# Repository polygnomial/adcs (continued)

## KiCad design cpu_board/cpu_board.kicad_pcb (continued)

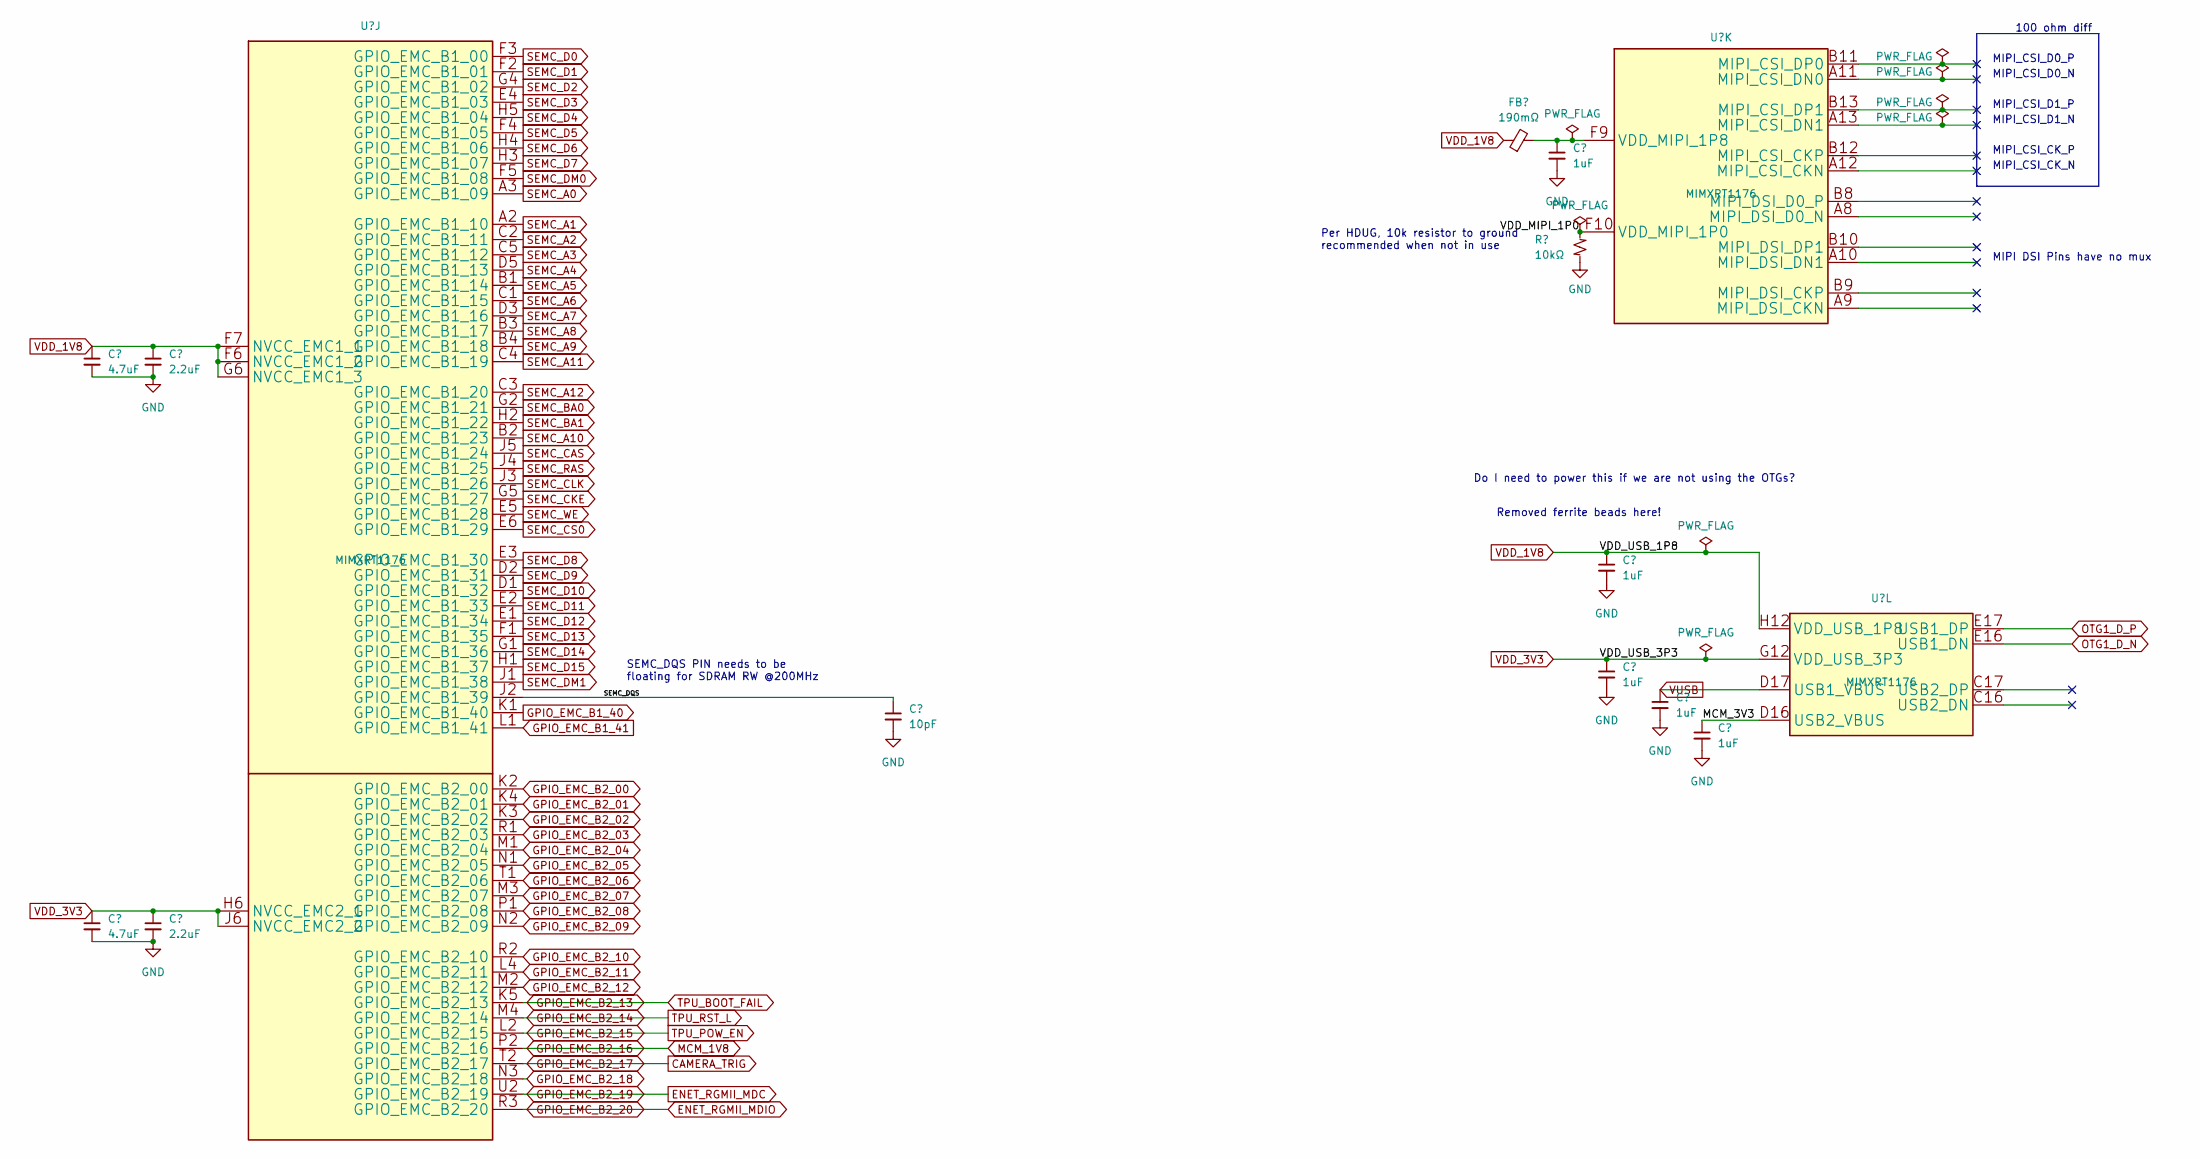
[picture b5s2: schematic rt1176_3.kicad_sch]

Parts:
C5: 10pF; Perfect_0201
C51, C52: 4.7uF; Perfect_0201
C53, C54: 2.2uF; Perfect_0201
C56, C58, C59, C61: 1uF; Perfect_0201
C60: 1uF; Perfect_0402
FB3: 190mΩ; Perfect_0402; JLCPCB P/N C85812
R10: 10kΩ; Perfect_0201
U2: MIMXRT1176; U_MIMXRT1176DVMAA_NXP; JLCPCB P/N C1020267

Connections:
/RT1176 #3/MCM_3V3: C61.1, U2.D16 (USB2_VBUS)
/RT1176 #3/SEMC_DQS: C5.1, U2.J2 (GPIO_EMC_B1_39)
CAMERA_TRIG: U2.T2 (GPIO_EMC_B2_17); also elsewhere on the board
ENET_RGMII_MDC: U2.U2 (GPIO_EMC_B2_19); also elsewhere on the board
ENET_RGMII_MDIO: U2.R3 (GPIO_EMC_B2_20); also elsewhere on the board
GPIO_EMC_B1_40: U2.K1 (GPIO_EMC_B1_40); also elsewhere on the board
GPIO_EMC_B1_41: U2.L1 (GPIO_EMC_B1_41); also elsewhere on the board
GPIO_EMC_B2_00: U2.K2 (GPIO_EMC_B2_00); also elsewhere on the board
GPIO_EMC_B2_01: U2.K4 (GPIO_EMC_B2_01); also elsewhere on the board
GPIO_EMC_B2_02: U2.K3 (GPIO_EMC_B2_02); also elsewhere on the board
GPIO_EMC_B2_03: U2.R1 (GPIO_EMC_B2_03); also elsewhere on the board
GPIO_EMC_B2_04: U2.M1 (GPIO_EMC_B2_04); also elsewhere on the board
GPIO_EMC_B2_05: U2.N1 (GPIO_EMC_B2_05); also elsewhere on the board
GPIO_EMC_B2_06: U2.T1 (GPIO_EMC_B2_06); also elsewhere on the board
GPIO_EMC_B2_07: U2.M3 (GPIO_EMC_B2_07); also elsewhere on the board
GPIO_EMC_B2_08: U2.P1 (GPIO_EMC_B2_08); also elsewhere on the board
GPIO_EMC_B2_09: U2.N2 (GPIO_EMC_B2_09); also elsewhere on the board
GPIO_EMC_B2_10: U2.R2 (GPIO_EMC_B2_10); also elsewhere on the board
GPIO_EMC_B2_11: U2.L4 (GPIO_EMC_B2_11); also elsewhere on the board
GPIO_EMC_B2_12: U2.M2 (GPIO_EMC_B2_12); also elsewhere on the board
GPIO_EMC_B2_13: U2.K5 (GPIO_EMC_B2_13); also elsewhere on the board
GPIO_EMC_B2_14: U2.M4 (GPIO_EMC_B2_14); also elsewhere on the board
GPIO_EMC_B2_15: U2.L2 (GPIO_EMC_B2_15); also elsewhere on the board
GPIO_EMC_B2_16: U2.P2 (GPIO_EMC_B2_16); also elsewhere on the board
GPIO_EMC_B2_18: U2.N3 (GPIO_EMC_B2_18); also elsewhere on the board
unnamed: C56.1, FB3.2, U2.F9 (VDD_MIPI_1P8)
OTG1_D_N: U2.E16 (USB1_DN); also elsewhere on the board
OTG1_D_P: U2.E17 (USB1_DP); also elsewhere on the board
SEMC_A0: U2.A3 (GPIO_EMC_B1_09); also elsewhere on the board
SEMC_A1: U2.A2 (GPIO_EMC_B1_10); also elsewhere on the board
SEMC_A2: U2.C2 (GPIO_EMC_B1_11); also elsewhere on the board
SEMC_A3: U2.C5 (GPIO_EMC_B1_12); also elsewhere on the board
SEMC_A4: U2.D5 (GPIO_EMC_B1_13); also elsewhere on the board
SEMC_A5: U2.B1 (GPIO_EMC_B1_14); also elsewhere on the board
SEMC_A6: U2.C1 (GPIO_EMC_B1_15); also elsewhere on the board
SEMC_A7: U2.D3 (GPIO_EMC_B1_16); also elsewhere on the board
SEMC_A8: U2.B3 (GPIO_EMC_B1_17); also elsewhere on the board
SEMC_A9: U2.B4 (GPIO_EMC_B1_18); also elsewhere on the board
SEMC_A10: U2.B2 (GPIO_EMC_B1_23); also elsewhere on the board
SEMC_A11: U2.C4 (GPIO_EMC_B1_19); also elsewhere on the board
SEMC_A12: U2.C3 (GPIO_EMC_B1_20); also elsewhere on the board
SEMC_BA0: U2.G2 (GPIO_EMC_B1_21); also elsewhere on the board
SEMC_BA1: U2.H2 (GPIO_EMC_B1_22); also elsewhere on the board
SEMC_CAS: U2.J5 (GPIO_EMC_B1_24); also elsewhere on the board
SEMC_CKE: U2.G5 (GPIO_EMC_B1_27); also elsewhere on the board
SEMC_CLK: U2.J3 (GPIO_EMC_B1_26); also elsewhere on the board
SEMC_CS0: U2.E6 (GPIO_EMC_B1_29); also elsewhere on the board
SEMC_D0: U2.F3 (GPIO_EMC_B1_00); also elsewhere on the board
SEMC_D1: U2.F2 (GPIO_EMC_B1_01); also elsewhere on the board
SEMC_D2: U2.G4 (GPIO_EMC_B1_02); also elsewhere on the board
SEMC_D3: U2.E4 (GPIO_EMC_B1_03); also elsewhere on the board
SEMC_D4: U2.H5 (GPIO_EMC_B1_04); also elsewhere on the board
SEMC_D5: U2.F4 (GPIO_EMC_B1_05); also elsewhere on the board
SEMC_D6: U2.H4 (GPIO_EMC_B1_06); also elsewhere on the board
SEMC_D7: U2.H3 (GPIO_EMC_B1_07); also elsewhere on the board
SEMC_D8: U2.E3 (GPIO_EMC_B1_30); also elsewhere on the board
SEMC_D9: U2.D2 (GPIO_EMC_B1_31); also elsewhere on the board
SEMC_D10: U2.D1 (GPIO_EMC_B1_32); also elsewhere on the board
SEMC_D11: U2.E2 (GPIO_EMC_B1_33); also elsewhere on the board
SEMC_D12: U2.E1 (GPIO_EMC_B1_34); also elsewhere on the board
SEMC_D13: U2.F1 (GPIO_EMC_B1_35); also elsewhere on the board
SEMC_D14: U2.G1 (GPIO_EMC_B1_36); also elsewhere on the board
SEMC_D15: U2.H1 (GPIO_EMC_B1_37); also elsewhere on the board
SEMC_DM0: U2.F5 (GPIO_EMC_B1_08); also elsewhere on the board
SEMC_DM1: U2.J1 (GPIO_EMC_B1_38); also elsewhere on the board
SEMC_RAS: U2.J4 (GPIO_EMC_B1_25); also elsewhere on the board
SEMC_WE: U2.E5 (GPIO_EMC_B1_28); also elsewhere on the board
VDD_1V8: C51.1, C53.1, C58.1, FB3.1, U2.F6 (NVCC_EMC1_2), U2.F7 (NVCC_EMC1_1), U2.G6 (NVCC_EMC1_3), U2.H12 (VDD_USB_1P8); also elsewhere on the board
VDD_3V3: C52.1, C54.1, C59.1, U2.G12 (VDD_USB_3P3), U2.H6 (NVCC_EMC2_1), U2.J6 (NVCC_EMC2_2); also elsewhere on the board
VUSB: C60.1, U2.D17 (USB1_VBUS); also elsewhere on the board

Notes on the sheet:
SEMC_DQS PIN needs to be floating for SDRAM RW @200MHz
100 ohm diff
MIPI_CSI_D1_P
MIPI_CSI_D0_P
Per HDUG, 10k resistor to ground recommended when not in use
MIPI_CSI_D0_N
MIPI_CSI_CK_P
Do I need to power this if we are not using the OTGs?
MIPI DSI Pins have no mux
Removed ferrite beads here!
MIPI_CSI_CK_N
MIPI_CSI_D1_N

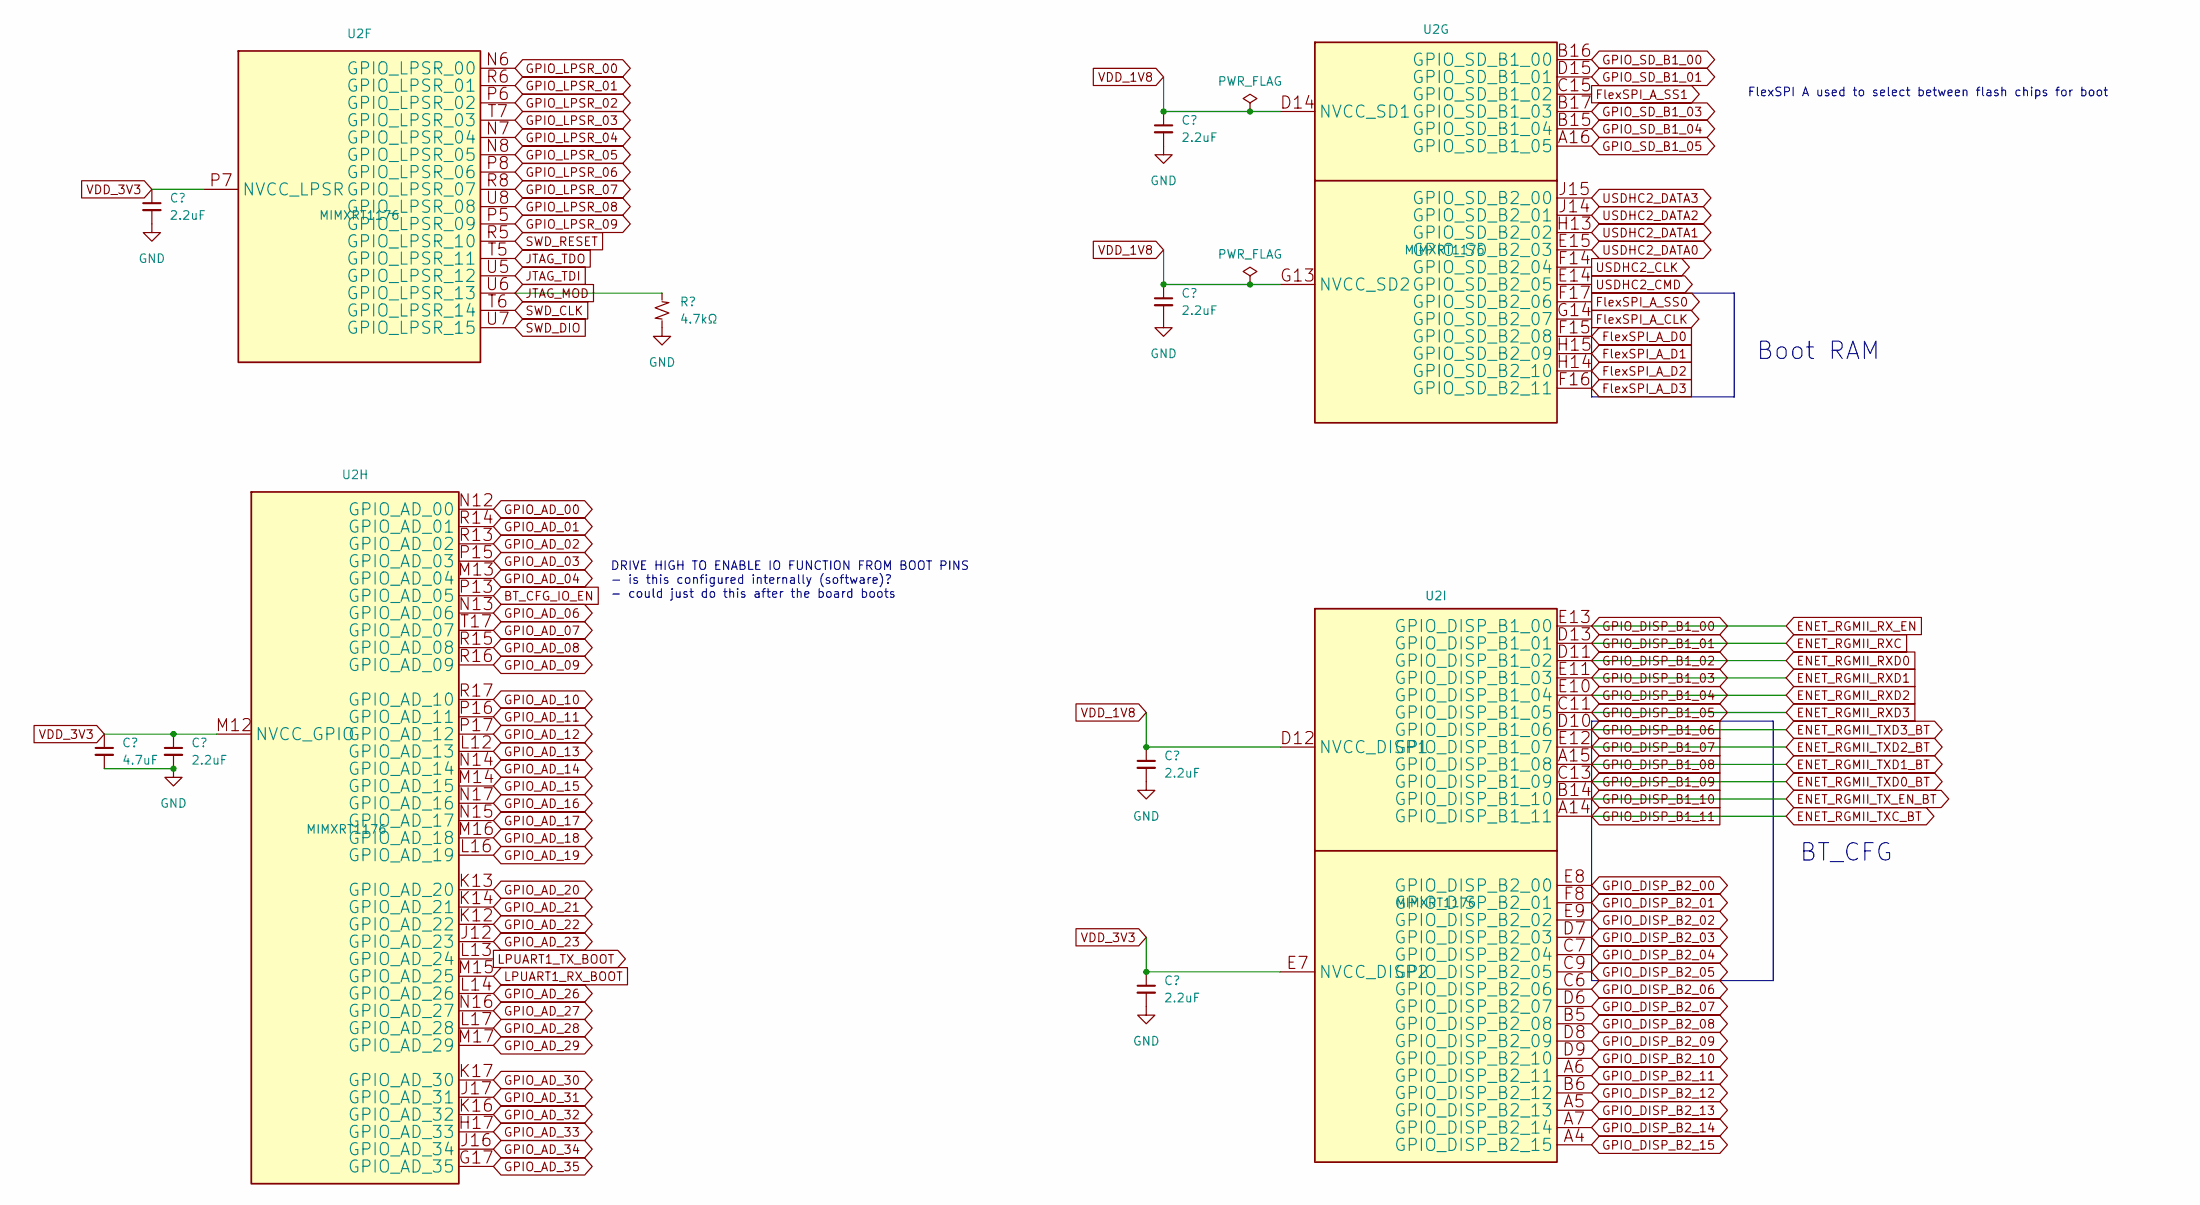
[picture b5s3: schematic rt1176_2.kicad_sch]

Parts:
C44: 4.7uF; Perfect_0201
C45, C46, C47, C48, C49, C50: 2.2uF; Perfect_0201
R10: 4.7kΩ; Perfect_0402
U2: MIMXRT1176; U_MIMXRT1176DVMAA_NXP; JLCPCB P/N C1020267

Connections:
BT_CFG_IO_EN: U2.P13 (GPIO_AD_05); also elsewhere on the board
ENET_RGMII_RXC: U2.D13 (GPIO_DISP_B1_01); also elsewhere on the board
ENET_RGMII_RXD0: U2.D11 (GPIO_DISP_B1_02); also elsewhere on the board
ENET_RGMII_RXD1: U2.E11 (GPIO_DISP_B1_03); also elsewhere on the board
ENET_RGMII_RXD2: U2.E10 (GPIO_DISP_B1_04); also elsewhere on the board
ENET_RGMII_RXD3: U2.C11 (GPIO_DISP_B1_05); also elsewhere on the board
ENET_RGMII_RX_EN: U2.E13 (GPIO_DISP_B1_00); also elsewhere on the board
ENET_RGMII_TXC_BT: U2.A14 (GPIO_DISP_B1_11); also elsewhere on the board
ENET_RGMII_TXD0_BT: U2.C13 (GPIO_DISP_B1_09); also elsewhere on the board
ENET_RGMII_TXD1_BT: U2.A15 (GPIO_DISP_B1_08); also elsewhere on the board
ENET_RGMII_TXD2_BT: U2.E12 (GPIO_DISP_B1_07); also elsewhere on the board
ENET_RGMII_TXD3_BT: U2.D10 (GPIO_DISP_B1_06); also elsewhere on the board
ENET_RGMII_TX_EN_BT: U2.B14 (GPIO_DISP_B1_10); also elsewhere on the board
FlexSPI_A_CLK: U2.G14 (GPIO_SD_B2_07); also elsewhere on the board
FlexSPI_A_D0: U2.F15 (GPIO_SD_B2_08); also elsewhere on the board
FlexSPI_A_D1: U2.H15 (GPIO_SD_B2_09); also elsewhere on the board
FlexSPI_A_D2: U2.H14 (GPIO_SD_B2_10); also elsewhere on the board
FlexSPI_A_D3: U2.F16 (GPIO_SD_B2_11); also elsewhere on the board
FlexSPI_A_SS0: U2.F17 (GPIO_SD_B2_06); also elsewhere on the board
FlexSPI_A_SS1: U2.C15 (GPIO_SD_B1_02); also elsewhere on the board
GPIO_AD_00: U2.N12 (GPIO_AD_00); also elsewhere on the board
GPIO_AD_01: U2.R14 (GPIO_AD_01); also elsewhere on the board
GPIO_AD_02: U2.R13 (GPIO_AD_02); also elsewhere on the board
GPIO_AD_03: U2.P15 (GPIO_AD_03); also elsewhere on the board
GPIO_AD_04: U2.M13 (GPIO_AD_04); also elsewhere on the board
GPIO_AD_06: U2.N13 (GPIO_AD_06); also elsewhere on the board
GPIO_AD_07: U2.T17 (GPIO_AD_07); also elsewhere on the board
GPIO_AD_08: U2.R15 (GPIO_AD_08); also elsewhere on the board
GPIO_AD_09: U2.R16 (GPIO_AD_09); also elsewhere on the board
GPIO_AD_10: U2.R17 (GPIO_AD_10); also elsewhere on the board
GPIO_AD_11: U2.P16 (GPIO_AD_11); also elsewhere on the board
GPIO_AD_12: U2.P17 (GPIO_AD_12); also elsewhere on the board
GPIO_AD_13: U2.L12 (GPIO_AD_13); also elsewhere on the board
GPIO_AD_14: U2.N14 (GPIO_AD_14); also elsewhere on the board
GPIO_AD_15: U2.M14 (GPIO_AD_15); also elsewhere on the board
GPIO_AD_16: U2.N17 (GPIO_AD_16); also elsewhere on the board
GPIO_AD_17: U2.N15 (GPIO_AD_17); also elsewhere on the board
GPIO_AD_18: U2.M16 (GPIO_AD_18); also elsewhere on the board
GPIO_AD_19: U2.L16 (GPIO_AD_19); also elsewhere on the board
GPIO_AD_20: U2.K13 (GPIO_AD_20); also elsewhere on the board
GPIO_AD_21: U2.K14 (GPIO_AD_21); also elsewhere on the board
GPIO_AD_22: U2.K12 (GPIO_AD_22); also elsewhere on the board
GPIO_AD_23: U2.J12 (GPIO_AD_23); also elsewhere on the board
GPIO_AD_26: U2.L14 (GPIO_AD_26); also elsewhere on the board
GPIO_AD_27: U2.N16 (GPIO_AD_27); also elsewhere on the board
GPIO_AD_28: U2.L17 (GPIO_AD_28); also elsewhere on the board
GPIO_AD_29: U2.M17 (GPIO_AD_29); also elsewhere on the board
GPIO_AD_30: U2.K17 (GPIO_AD_30); also elsewhere on the board
GPIO_AD_31: U2.J17 (GPIO_AD_31); also elsewhere on the board
GPIO_AD_32: U2.K16 (GPIO_AD_32); also elsewhere on the board
GPIO_AD_33: U2.H17 (GPIO_AD_33); also elsewhere on the board
GPIO_AD_34: U2.J16 (GPIO_AD_34); also elsewhere on the board
GPIO_AD_35: U2.G17 (GPIO_AD_35); also elsewhere on the board
GPIO_DISP_B2_00: U2.E8 (GPIO_DISP_B2_00); also elsewhere on the board
GPIO_DISP_B2_01: U2.F8 (GPIO_DISP_B2_01); also elsewhere on the board
GPIO_DISP_B2_02: U2.E9 (GPIO_DISP_B2_02); also elsewhere on the board
GPIO_DISP_B2_03: U2.D7 (GPIO_DISP_B2_03); also elsewhere on the board
GPIO_DISP_B2_04: U2.C7 (GPIO_DISP_B2_04); also elsewhere on the board
GPIO_DISP_B2_05: U2.C9 (GPIO_DISP_B2_05); also elsewhere on the board
GPIO_DISP_B2_06: U2.C6 (GPIO_DISP_B2_06); also elsewhere on the board
GPIO_DISP_B2_07: U2.D6 (GPIO_DISP_B2_07); also elsewhere on the board
GPIO_DISP_B2_08: U2.B5 (GPIO_DISP_B2_08); also elsewhere on the board
GPIO_DISP_B2_09: U2.D8 (GPIO_DISP_B2_09); also elsewhere on the board
GPIO_DISP_B2_10: U2.D9 (GPIO_DISP_B2_10); also elsewhere on the board
GPIO_DISP_B2_11: U2.A6 (GPIO_DISP_B2_11); also elsewhere on the board
GPIO_DISP_B2_12: U2.B6 (GPIO_DISP_B2_12); also elsewhere on the board
GPIO_DISP_B2_13: U2.A5 (GPIO_DISP_B2_13); also elsewhere on the board
GPIO_DISP_B2_14: U2.A7 (GPIO_DISP_B2_14); also elsewhere on the board
GPIO_DISP_B2_15: U2.A4 (GPIO_DISP_B2_15); also elsewhere on the board
GPIO_LPSR_00: U2.N6 (GPIO_LPSR_00); also elsewhere on the board
GPIO_LPSR_01: U2.R6 (GPIO_LPSR_01); also elsewhere on the board
GPIO_LPSR_02: U2.P6 (GPIO_LPSR_02); also elsewhere on the board
GPIO_LPSR_03: U2.T7 (GPIO_LPSR_03); also elsewhere on the board
GPIO_LPSR_04: U2.N7 (GPIO_LPSR_04); also elsewhere on the board
GPIO_LPSR_05: U2.N8 (GPIO_LPSR_05); also elsewhere on the board
GPIO_LPSR_06: U2.P8 (GPIO_LPSR_06); also elsewhere on the board
GPIO_LPSR_07: U2.R8 (GPIO_LPSR_07); also elsewhere on the board
GPIO_LPSR_08: U2.U8 (GPIO_LPSR_08); also elsewhere on the board
GPIO_LPSR_09: U2.P5 (GPIO_LPSR_09); also elsewhere on the board
GPIO_SD_B1_00: U2.B16 (GPIO_SD_B1_00); also elsewhere on the board
GPIO_SD_B1_01: U2.D15 (GPIO_SD_B1_01); also elsewhere on the board
GPIO_SD_B1_03: U2.B17 (GPIO_SD_B1_03); also elsewhere on the board
GPIO_SD_B1_04: U2.B15 (GPIO_SD_B1_04); also elsewhere on the board
GPIO_SD_B1_05: U2.A16 (GPIO_SD_B1_05); also elsewhere on the board
JTAG_TDI: U2.U5 (GPIO_LPSR_12); also elsewhere on the board
JTAG_TDO: U2.T5 (GPIO_LPSR_11); also elsewhere on the board
LPUART1_RX_BOOT: U2.M15 (GPIO_AD_25); also elsewhere on the board
LPUART1_TX_BOOT: U2.L13 (GPIO_AD_24)
SWD_CLK: U2.T6 (GPIO_LPSR_14); also elsewhere on the board
SWD_DIO: U2.U7 (GPIO_LPSR_15); also elsewhere on the board
SWD_RESET: U2.R5 (GPIO_LPSR_10); also elsewhere on the board
USDHC2_CLK: U2.F14 (GPIO_SD_B2_04); also elsewhere on the board
USDHC2_CMD: U2.E14 (GPIO_SD_B2_05); also elsewhere on the board
USDHC2_DATA0: U2.E15 (GPIO_SD_B2_03); also elsewhere on the board
USDHC2_DATA1: U2.H13 (GPIO_SD_B2_02); also elsewhere on the board
USDHC2_DATA2: U2.J14 (GPIO_SD_B2_01); also elsewhere on the board
USDHC2_DATA3: U2.J15 (GPIO_SD_B2_00); also elsewhere on the board
VDD_1V8: C47.1, C49.1, C50.1, U2.D12 (NVCC_DISP1), U2.D14 (NVCC_SD1), U2.G13 (NVCC_SD2); also elsewhere on the board
VDD_3V3: C44.1, C45.1, C46.1, C48.1, U2.E7 (NVCC_DISP2), U2.M12 (NVCC_GPIO), U2.P7 (NVCC_LPSR); also elsewhere on the board

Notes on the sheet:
FlexSPI A used to select between flash chips for boot
DRIVE HIGH TO ENABLE IO FUNCTION FROM BOOT PINS - is this configured internally (software)? - could just do this after the board boots
Boot RAM
BT_CFG

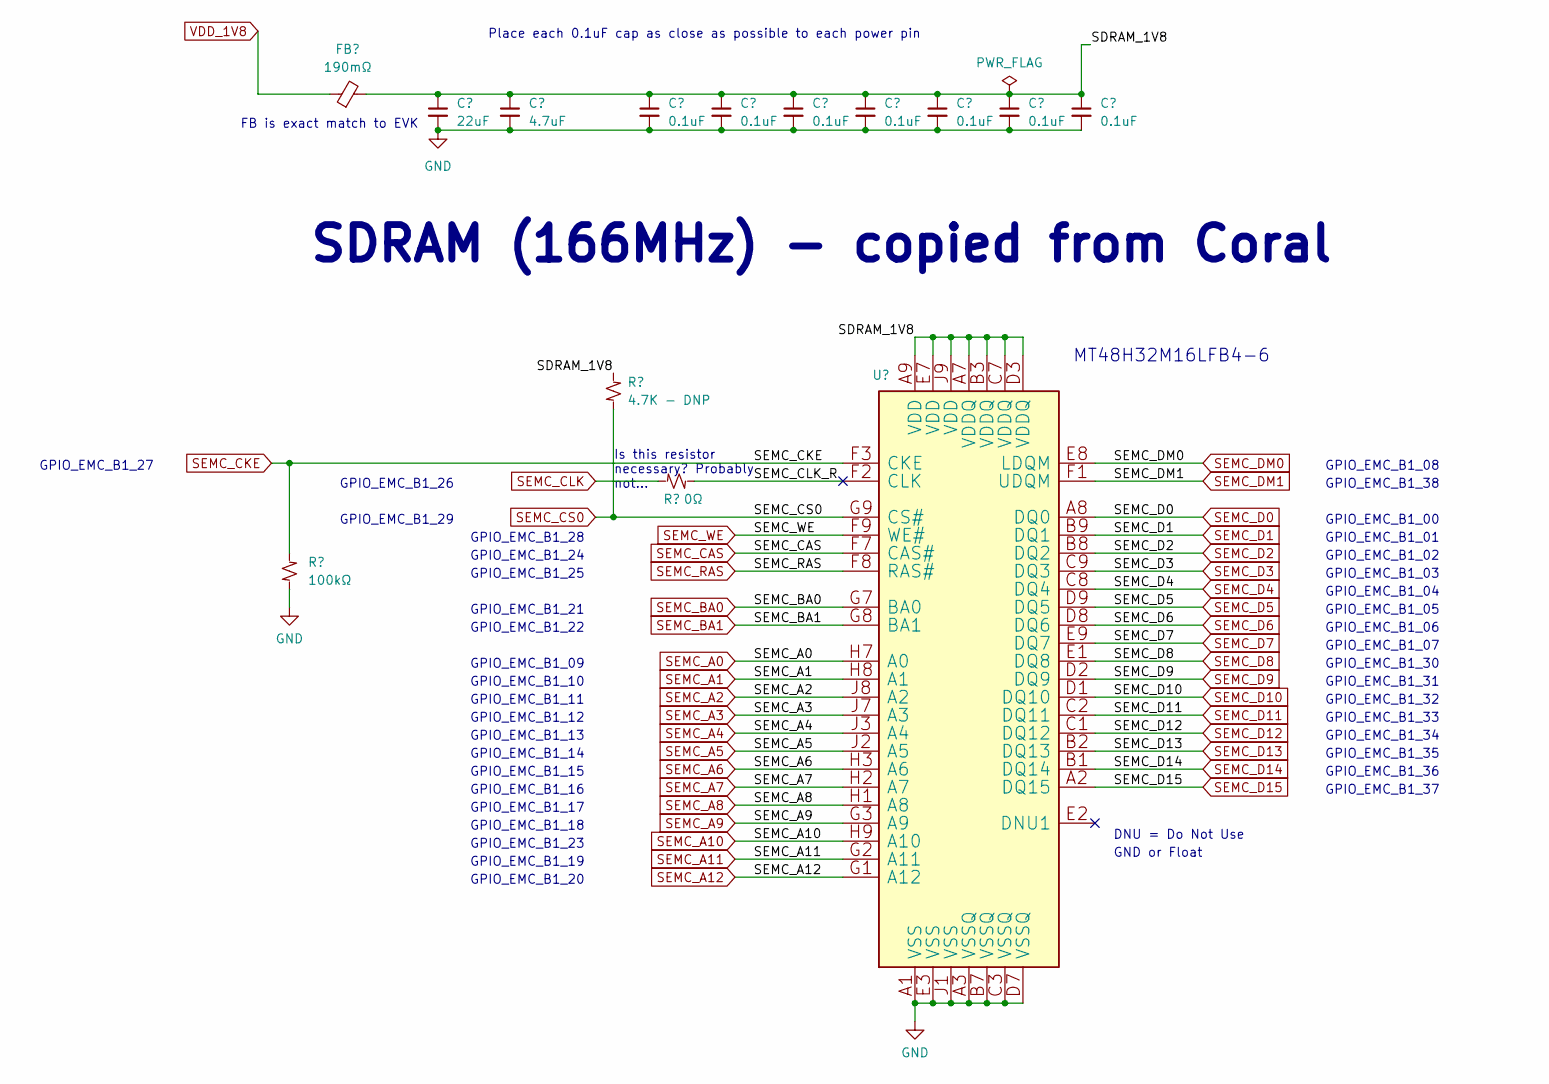
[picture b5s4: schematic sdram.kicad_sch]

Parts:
C67: 22uF; C_0603_1608Metric
C68: 4.7uF; Perfect_0402
C69, C70, C71, C72, C73, C74, C75: 0.1uF; Perfect_0201
FB6: 190mΩ; Perfect_0402; JLCPCB P/N C85812
R24: 100kΩ; Perfect_0402
R25: 4.7K - DNP; Perfect_0402
R26: 0Ω; Perfect_0402
U6: MT48H32M16LFB4-6; VFBGA54_8X8_MRN; JLCPCB P/N C1351581

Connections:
/SDRAM/SDRAM_1V8: C67.1, C68.1, C69.1, C70.1, C71.1, C72.1, C73.1, C74.1, C75.1, FB6.2, R25.1, U6.A7 (VDDQ), U6.A9 (VDD), U6.B3 (VDDQ), U6.C7 (VDDQ), U6.D3 (VDDQ), U6.E7 (VDD), U6.J9 (VDD)
/SDRAM/SEMC_CLK_R: R26.2, U6.F2 (CLK)
SEMC_A0: U6.H7 (A0); also elsewhere on the board
SEMC_A1: U6.H8 (A1); also elsewhere on the board
SEMC_A2: U6.J8 (A2); also elsewhere on the board
SEMC_A3: U6.J7 (A3); also elsewhere on the board
SEMC_A4: U6.J3 (A4); also elsewhere on the board
SEMC_A5: U6.J2 (A5); also elsewhere on the board
SEMC_A6: U6.H3 (A6); also elsewhere on the board
SEMC_A7: U6.H2 (A7); also elsewhere on the board
SEMC_A8: U6.H1 (A8); also elsewhere on the board
SEMC_A9: U6.G3 (A9); also elsewhere on the board
SEMC_A10: U6.H9 (A10); also elsewhere on the board
SEMC_A11: U6.G2 (A11); also elsewhere on the board
SEMC_A12: U6.G1 (A12); also elsewhere on the board
SEMC_BA0: U6.G7 (BA0); also elsewhere on the board
SEMC_BA1: U6.G8 (BA1); also elsewhere on the board
SEMC_CAS: U6.F7 (CAS#); also elsewhere on the board
SEMC_CKE: R24.1, U6.F3 (CKE); also elsewhere on the board
SEMC_CLK: R26.1; also elsewhere on the board
SEMC_CS0: R25.2, U6.G9 (CS#); also elsewhere on the board
SEMC_D0: U6.A8 (DQ0); also elsewhere on the board
SEMC_D1: U6.B9 (DQ1); also elsewhere on the board
SEMC_D2: U6.B8 (DQ2); also elsewhere on the board
SEMC_D3: U6.C9 (DQ3); also elsewhere on the board
SEMC_D4: U6.C8 (DQ4); also elsewhere on the board
SEMC_D5: U6.D9 (DQ5); also elsewhere on the board
SEMC_D6: U6.D8 (DQ6); also elsewhere on the board
SEMC_D7: U6.E9 (DQ7); also elsewhere on the board
SEMC_D8: U6.E1 (DQ8); also elsewhere on the board
SEMC_D9: U6.D2 (DQ9); also elsewhere on the board
SEMC_D10: U6.D1 (DQ10); also elsewhere on the board
SEMC_D11: U6.C2 (DQ11); also elsewhere on the board
SEMC_D12: U6.C1 (DQ12); also elsewhere on the board
SEMC_D13: U6.B2 (DQ13); also elsewhere on the board
SEMC_D14: U6.B1 (DQ14); also elsewhere on the board
SEMC_D15: U6.A2 (DQ15); also elsewhere on the board
SEMC_DM0: U6.E8 (LDQM); also elsewhere on the board
SEMC_DM1: U6.F1 (UDQM); also elsewhere on the board
SEMC_RAS: U6.F8 (RAS#); also elsewhere on the board
SEMC_WE: U6.F9 (WE#); also elsewhere on the board
VDD_1V8: FB6.1; also elsewhere on the board

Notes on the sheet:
GPIO_EMC_B1_08
GPIO_EMC_B1_30
GPIO_EMC_B1_18
GPIO_EMC_B1_25
GPIO_EMC_B1_36
FB is exact match to EVK
GPIO_EMC_B1_10
GPIO_EMC_B1_14
GPIO_EMC_B1_15
GPIO_EMC_B1_34
GPIO_EMC_B1_17
GPIO_EMC_B1_29
GPIO_EMC_B1_05
GPIO_EMC_B1_00
GPIO_EMC_B1_31
GPIO_EMC_B1_01
GPIO_EMC_B1_03
GPIO_EMC_B1_33
GPIO_EMC_B1_02
Place each 0.1uF cap as close as possible to each power pin
GPIO_EMC_B1_28
GPIO_EMC_B1_22
GPIO_EMC_B1_24
GPIO_EMC_B1_35
MT48H32M16LFB4-6
GPIO_EMC_B1_20
GPIO_EMC_B1_06
GPIO_EMC_B1_16
GPIO_EMC_B1_38
GPIO_EMC_B1_04
GPIO_EMC_B1_23
GPIO_EMC_B1_26
DNU = Do Not Use
GPIO_EMC_B1_09
GND or Float
GPIO_EMC_B1_13
GPIO_EMC_B1_11
GPIO_EMC_B1_37
GPIO_EMC_B1_21
GPIO_EMC_B1_27

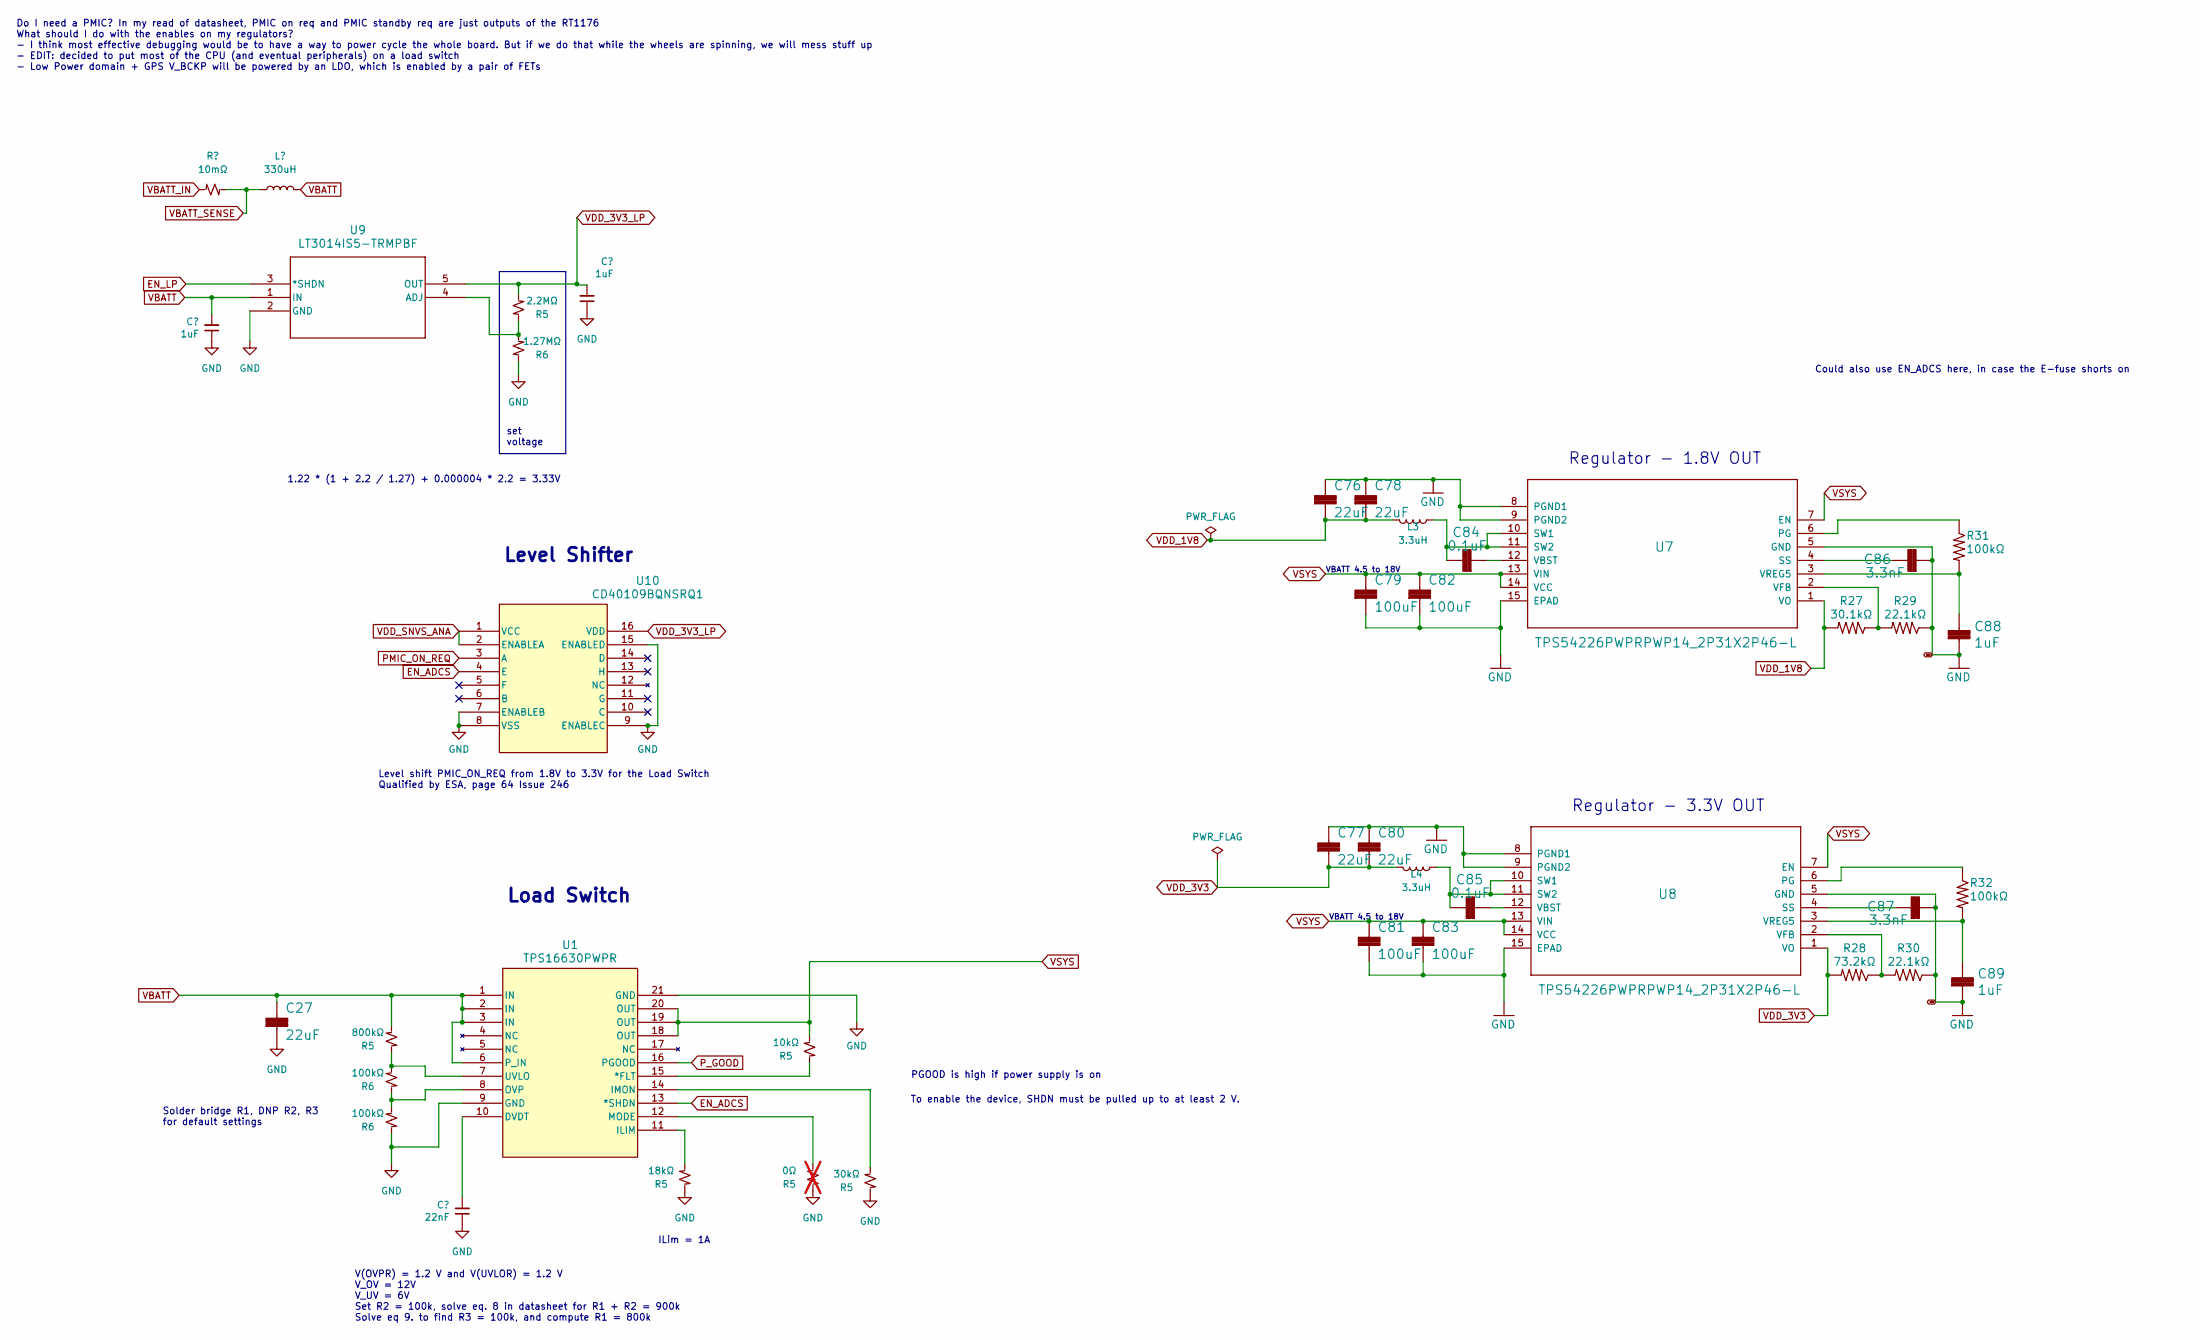
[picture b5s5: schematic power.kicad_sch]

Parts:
C1, C2, C88, C89: 1uF; Perfect_0402
C27, C76, C77, C78, C80: 22uF; C_0603_1608Metric
C79, C81, C82, C83: 100uF; C_1210_3225Metric
C84, C85: 0.1uF; Perfect_0402
C86, C87: 3.3nF; Perfect_0402
L3, L4: 3.3uH; L_2141; JLCPCB P/N C304367
L5: 330uH; IND_SRN6045TA-331K; JLCPCB P/N C2049953
R1: 10mΩ; R_2512_6332Metric
R5: 18kΩ; Perfect_0402
R6, R31, R32: 100kΩ; Perfect_0402
R27: 30.1kΩ; Perfect_0402
R28: 73.2kΩ; Perfect_0402
R29, R30: 22.1kΩ; Perfect_0402
U1: TPS16630PWPR; HTSSOP20_PWP_TEX
U7, U8: TPS54226PWPRPWP14_2P31X2P46-L; PWP14_2P31X2P46-L; JLCPCB P/N C72066
U9: LT3014IS5-TRMPBF; S_5_ADI; JLCPCB P/N C666272
U10: CD40109BQNSRQ1; NS16

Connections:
EN_ADCS: U1.13 (*SHDN), U10.4 (E); also elsewhere on the board
EN_LP: U9.3 (*SHDN); also elsewhere on the board
unnamed: R31.1, U7.6 (PG)
unnamed: C86.1, U7.4 (SS)
unnamed: C84.1, L3.1, U7.10 (SW1), U7.11 (SW2)
unnamed: C84.2, U7.12 (VBST)
unnamed: R27.1, R29.2, U7.2 (VFB)
unnamed: C88.1, R31.2, U7.3 (VREG5)
unnamed: R32.1, U8.6 (PG)
unnamed: C87.1, U8.4 (SS)
unnamed: C85.1, L4.1, U8.10 (SW1), U8.11 (SW2)
unnamed: C85.2, U8.12 (VBST)
unnamed: R28.1, R30.2, U8.2 (VFB)
unnamed: C89.1, R32.2, U8.3 (VREG5)
PMIC_ON_REQ: U10.3 (A); also elsewhere on the board
P_GOOD: U1.16 (PGOOD); also elsewhere on the board
VBATT_IN: R1.1; also elsewhere on the board
VBATT_SENSE: R1.2; also elsewhere on the board
VDD_1V8: C76.2, C78.2, L3.2, R27.2, U7.1 (VO); also elsewhere on the board
VDD_3V3: C77.2, C80.2, L4.2, R28.2, U8.1 (VO); also elsewhere on the board
VDD_SNVS_ANA: U10.1 (VCC), U10.2 (ENABLEA); also elsewhere on the board

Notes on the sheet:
ILim = 1A
Regulator - 1.8V OUT
Level shift PMIC_ON_REQ from 1.8V to 3.3V for the Load Switch Qualified by ESA, page 64 Issue 246
set voltage
VBATT 4.5 to 18V
1.22 * (1 + 2.2 / 1.27) + 0.000004 * 2.2 = 3.33V
V(OVPR) = 1.2 V and V(UVLOR) = 1.2 V V_OV = 12V V_UV = 6V Set R2 = 100k, solve eq. 8 in datasheet for R1 + R2 = 900k Solve eq 9. to find R3 = 100k, and compute R1 = 800k
Could also use EN_ADCS here, in case the E-fuse shorts on
Solder bridge R1, DNP R2, R3 for default settings
Level Shifter
Regulator - 3.3V OUT
To enable the device, SHDN must be pulled up to at least 2 V.
Load Switch
Do I need a PMIC? In my read of datasheet, PMIC on req and PMIC standby req are just outputs of the RT1176 What should I do with the enables on my regulators? - I think most effective debugging would be to have a way to power cycle the whole board. But if we do that while the wheels are spinning, w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
PGOOD is high if power supply is on
